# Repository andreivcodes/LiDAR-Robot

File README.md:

.png)
.png)
.png)
.png)
.png)
.png)
.png)
.png)
.png)
.png)
.png)
.png)
.png)

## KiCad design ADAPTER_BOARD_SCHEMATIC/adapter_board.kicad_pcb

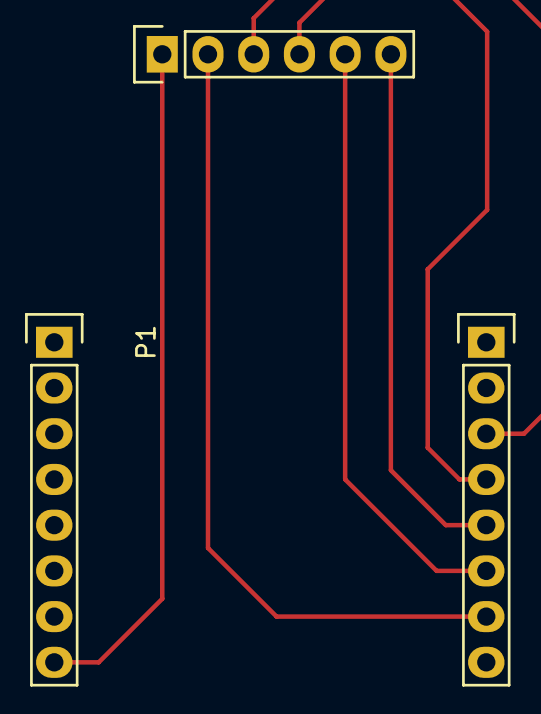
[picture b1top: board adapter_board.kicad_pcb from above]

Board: 2 copper layers, 3 parts (0 on the bottom side), 6 nets.

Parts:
P1: WEMO_1; Socket_Strip_Straight_1x08
P2: VL53L0X; Socket_Strip_Straight_1x06
P3: WEMO_2; Socket_Strip_Straight_1x08

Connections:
/3.3V: P1.8, P2.1
/ESP_D3: P2.6, P3.5
/ESP_D4: P2.5, P3.6
/ESP_SCL: P2.3, P3.3
/ESP_SDA: P2.4, P3.4
/GND: P2.2, P3.7

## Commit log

2016-12-04 Cleanup
2017-01-16 Rebuild
2017-01-16 Rebuild 2
2017-03-06 servo
2017-03-13 updatez
2017-04-03 Almost ready
2017-04-13 Circle screen updatz
2017-05-23 updatex
2017-06-09 ESP8266 OTA Update <3
2017-06-29 V1.0 functional radar and functional movement. Still have to combine them
2017-07-17 v1.0
2017-08-02 documentatie 1.0
2017-08-08 updatz
2017-08-17 updatz and fotoz
2017-08-29 lots of shiz
2017-09-04 updatz text
2017-09-11 added
